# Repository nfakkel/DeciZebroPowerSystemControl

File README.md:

# DeciZebroPowerSystemControl
This repository contains the microcontroller firmware code, the data analysis code and schematics. All are discussed in the Bachelor Thesis: Development of Power System Control for the DeciZebro

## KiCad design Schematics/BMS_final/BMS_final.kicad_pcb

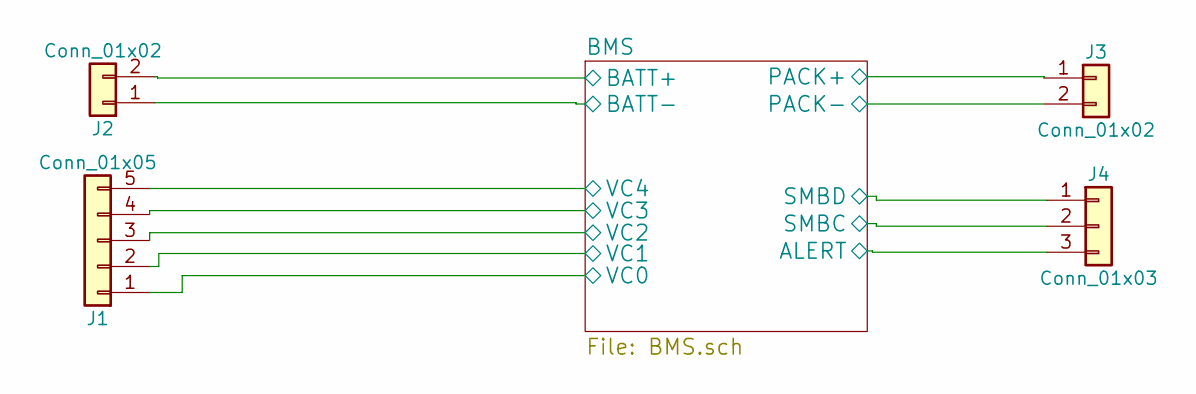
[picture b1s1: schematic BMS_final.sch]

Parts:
J1: Conn_01x05; JST_XH_B05B-XH-A_05x2.50mm_Straight
J2, J3: Conn_01x02; JST_VH_B2P-VH-FB-B_2x3.96mm_Vertical
J4: Conn_01x03; Pin_Header_Straight_1x03_Pitch2.54mm

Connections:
/BMS/ALERT: J4.3; also elsewhere on the board
/BMS/BATT+: J1.5, J2.2; also elsewhere on the board
/BMS/BATT-: J1.1, J2.1; also elsewhere on the board
/BMS/PACK+: J3.1; also elsewhere on the board
/BMS/PACK-: J3.2; also elsewhere on the board
/BMS/SMBC: J4.2; also elsewhere on the board
/BMS/SMBD: J4.1; also elsewhere on the board
/BMS/VC1: J1.2; also elsewhere on the board
/BMS/VC2: J1.3; also elsewhere on the board
/BMS/VC3: J1.4; also elsewhere on the board

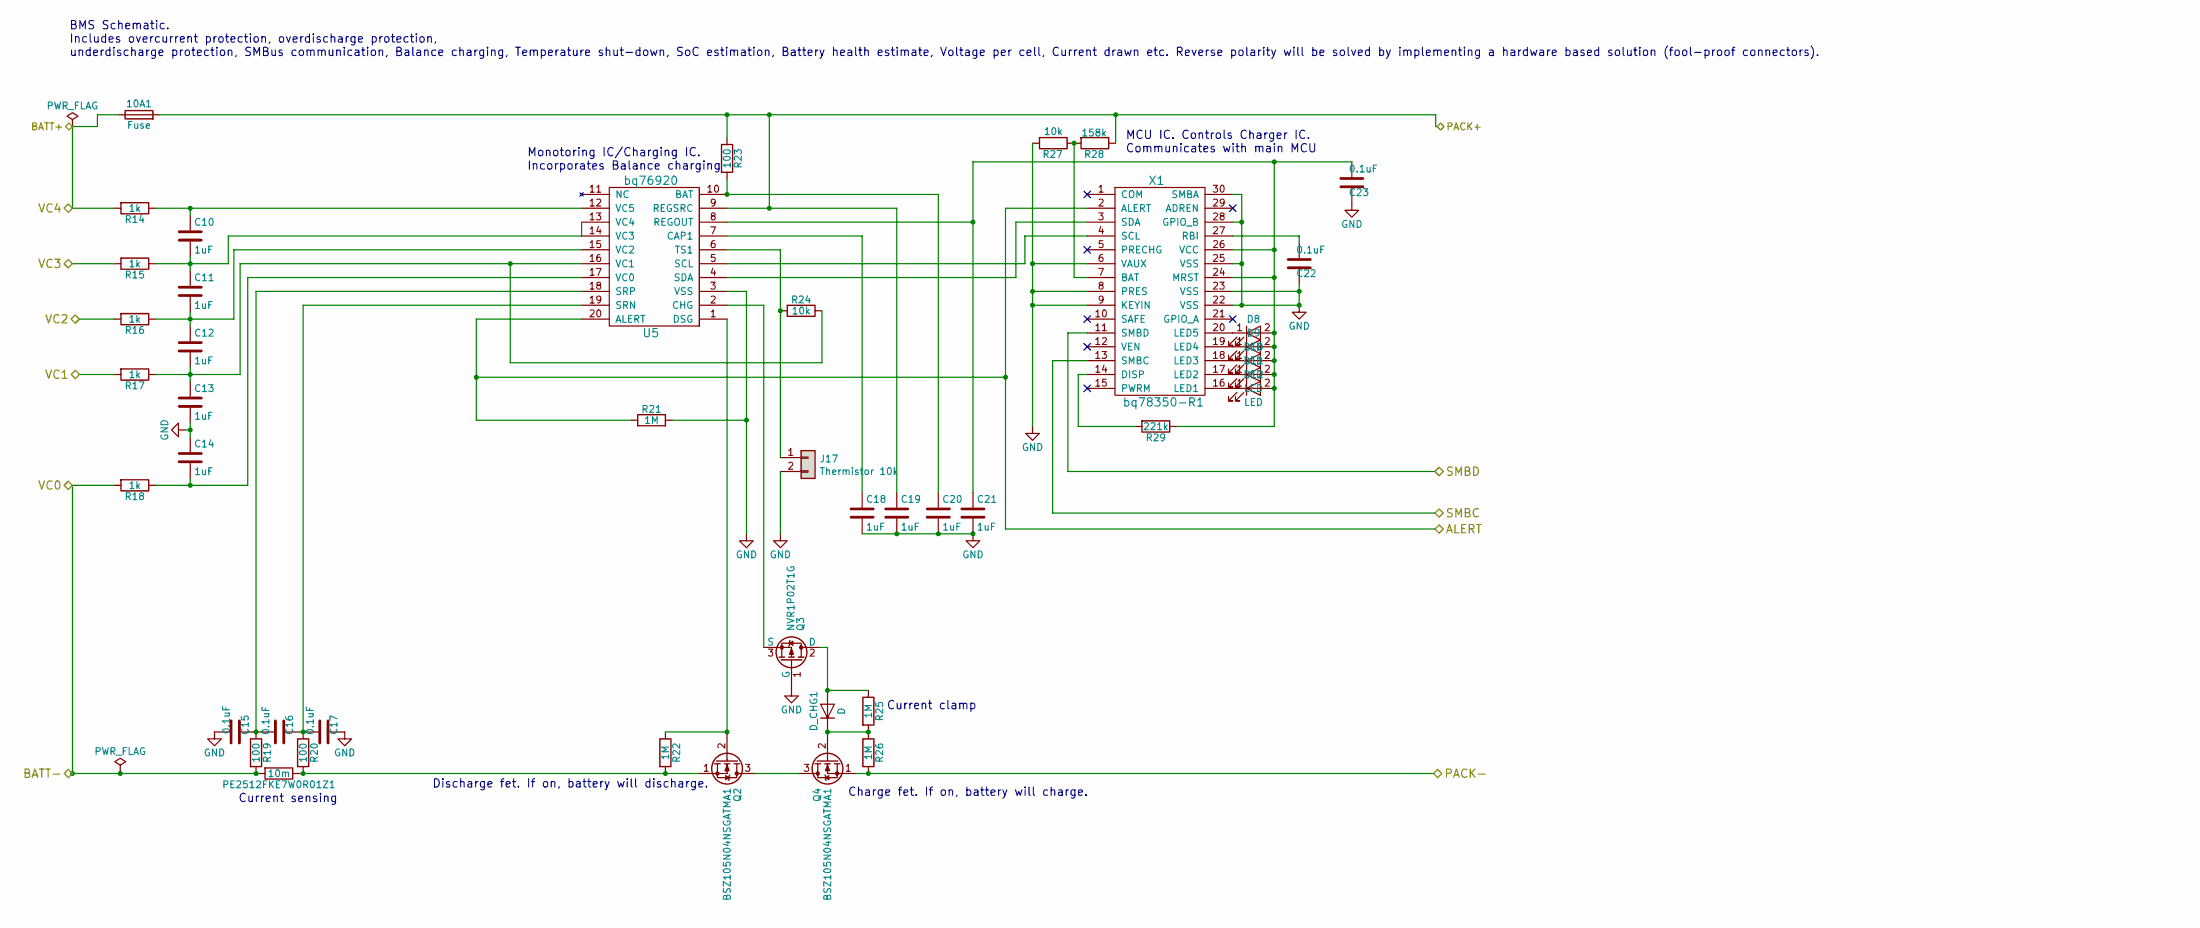
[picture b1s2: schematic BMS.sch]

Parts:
10A1: Fuse
C10, C11, C12, C13, C14, C18, C19, C20, C21: 1uF; C_0603
C15, C16, C17, C22, C23: 0.1uF; C_0402
D8, D9, D10, D11, D12: LED; LED_0603
D_CHG1: D; D_SOD-323
J17: Thermistor 10k; PINHEAD1-2
PE2512FKE7W0R01Z1: 10m; R_2512
Q2, Q4: BSZ105N04NSGATMA1; TO-263-2
Q3: NVR1P02T1G; SOT-23
R14, R15, R16, R17, R18: 1k; R_0402
R19, R20, R23: 100; R_0402
R21, R22, R25, R26: 1M; R_0603
R24, R27: 10k; R_0603
R28: 158k; R_0603
R29: 221k; R_0603
U5: bq76920; TSSOP-20_4.4x6.5mm_Pitch0.65mm
X1: bq78350-R1; TSSOP-30_4.4x7.8mm_P0.5mm

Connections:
/BMS/ALERT: R21.1, U5.20 (ALERT), X1.2 (ALERT); also elsewhere on the board
/BMS/BATT+: 10A1.1, R14.2; also elsewhere on the board
/BMS/BATT-: PE2512FKE7W0R01Z1.2, R18.2, R19.2; also elsewhere on the board
/BMS/PACK+: 10A1.2, C19.1, R23.1, R28.1, U5.9 (REGSRC); also elsewhere on the board
/BMS/PACK-: Q4.1 (S), R26.2; also elsewhere on the board
/BMS/SMBC: X1.13 (SMBC); also elsewhere on the board
/BMS/SMBD: X1.11 (SMBD); also elsewhere on the board
/BMS/VC1: R17.2; also elsewhere on the board
/BMS/VC2: R16.2; also elsewhere on the board
/BMS/VC3: R15.2; also elsewhere on the board
GND: C13.2, C14.1, C15.2, C17.1, C18.2, C19.2, C20.2, C21.2, C22.1, C23.1, J17.2, Q3.1 (G), R21.2, R27.2, U5.3 (VSS), X1.6 (VAUX), X1.8 (PRES), X1.9 (KEYIN), X1.22 (VSS), X1.23 (VSS), X1.25 (VSS), X1.28 (GPIO_B), X1.30 (SMBA)
unnamed: C10.1, R14.1, U5.12 (VC5)
unnamed: C10.2, C11.1, R15.1, U5.13 (VC4), U5.14 (VC3)
unnamed: C11.2, C12.1, R16.1, U5.15 (VC2)
unnamed: C12.2, C13.1, R17.1, R24.1, U5.16 (VC1)
unnamed: C14.2, R18.1, U5.17 (VC0)
unnamed: C15.1, C16.2, R19.1, U5.18 (SRP)
unnamed: C16.1, C17.2, R20.1, U5.19 (SRN)
unnamed: C18.1, U5.7 (CAP1)
unnamed: C20.1, R23.2, U5.10 (BAT)
unnamed: C21.1, C23.2, D8.2 (A), D9.2 (A), D10.2 (A), D11.2 (A), D12.2 (A), R29.1, U5.8 (REGOUT), X1.24 (MRST), X1.26 (VCC)
unnamed: C22.2, X1.27 (RBI)
unnamed: D8.1 (K), X1.20 (LED5)
unnamed: D9.1 (K), X1.19 (LED4)
unnamed: D10.1 (K), X1.18 (LED3)
unnamed: D11.1 (K), X1.17 (LED2)
unnamed: D12.1 (K), X1.16 (LED1)
unnamed: D_CHG1.1 (K), Q4.2 (G), R25.2, R26.1
unnamed: D_CHG1.2 (A), Q3.2 (D), R25.1
unnamed: J17.1, R24.2, U5.6 (TS1)
unnamed: PE2512FKE7W0R01Z1.1, Q2.1 (S), R20.2, R22.2
unnamed: Q2.2 (G), R22.1, U5.1 (DSG)
unnamed: Q2.3 (D), Q4.3 (D)
unnamed: Q3.3 (S), U5.2 (CHG)
unnamed: R27.1, R28.2, X1.7 (BAT)
unnamed: R29.2, X1.14 (DISP)
unnamed: U5.4 (SDA), X1.3 (SDA)
unnamed: U5.5 (SCL), X1.4 (SCL)

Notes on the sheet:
Charge fet. If on, battery will charge.
Discharge fet. If on, battery will discharge.
Current clamp
Current sensing
Monotoring IC/Charging IC. Incorporates Balance charging
MCU IC. Controls Charger IC. Communicates with main MCU
BMS Schematic. Includes overcurrent protection, overdischarge protection, underdischarge protection, SMBus communication, Balance charging, Temperature shut-down, SoC estimation, Battery health estimate, Voltage per cell, Current drawn etc. Reverse polarity will be solved by implementing a hardware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

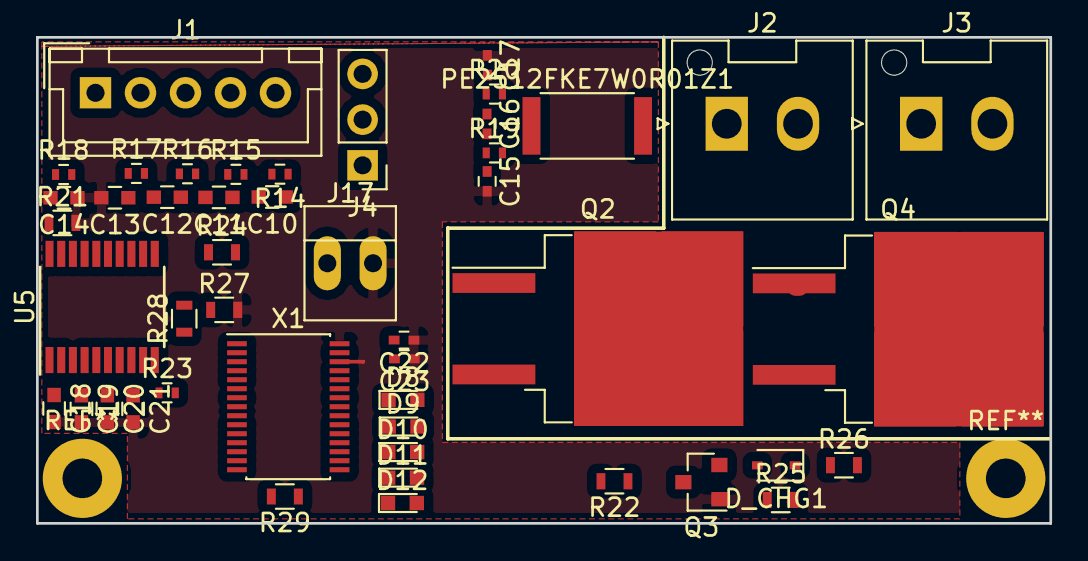
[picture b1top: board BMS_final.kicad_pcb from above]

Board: 4 copper layers, 56.3 x 27.0 mm, 47 parts (0 on the bottom side), 38 nets.

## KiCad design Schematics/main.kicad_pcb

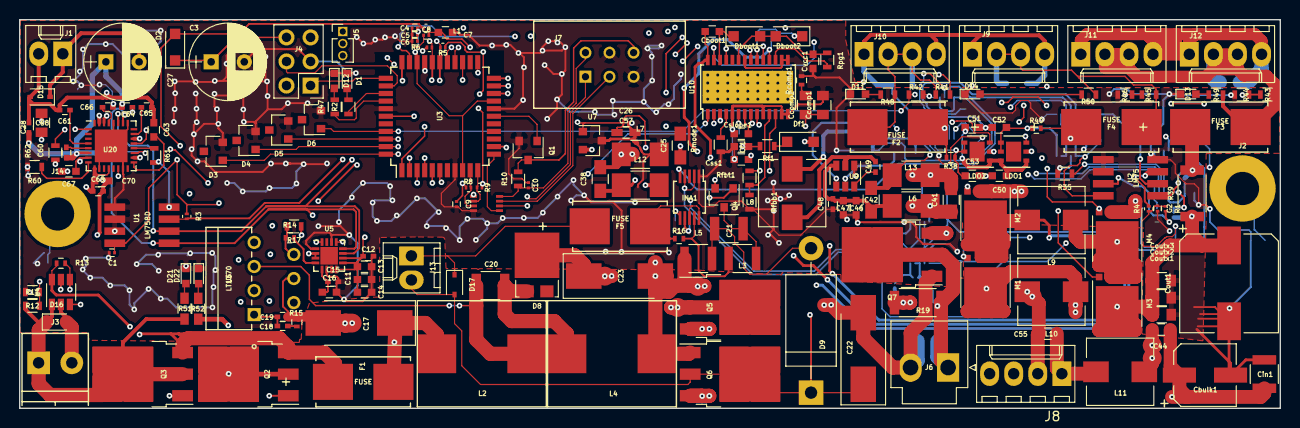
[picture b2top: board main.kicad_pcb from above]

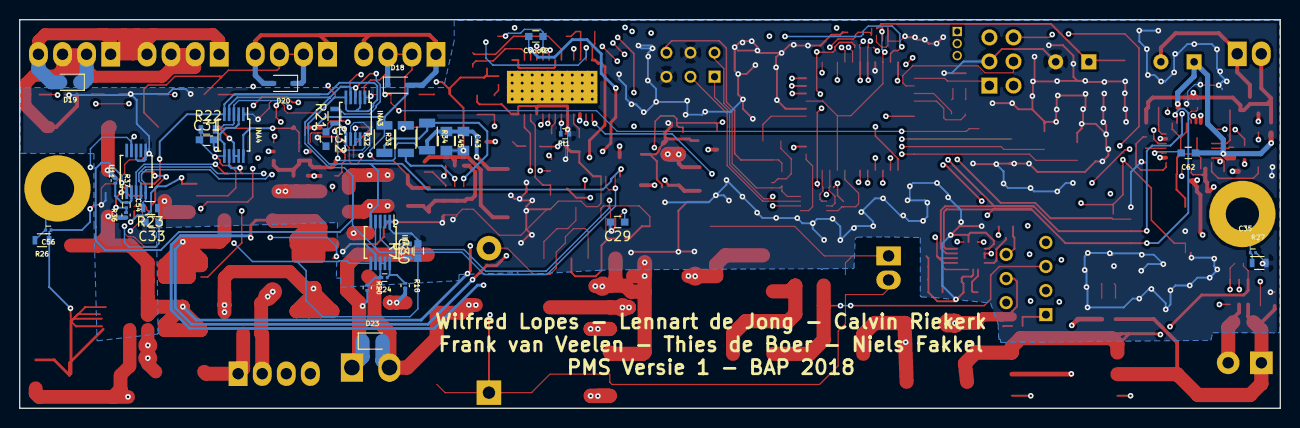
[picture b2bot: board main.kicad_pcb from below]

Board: 4 copper layers, 133.0 x 41.0 mm, 218 parts (35 on the bottom side), 131 nets.

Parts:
C1, C2, C10: 0.1u; C_0201
C3: 1m; CP_Radial_D8.0mm_P3.50mm
C4, C5, C6, C8, C9, C24, C26: .1u; C_0201
C7, C13, C14, C16: 10u; C_0603
C11: 0.1u; C_0603
C12, C15: 0.1u; C_0402
C17, C22, C23: 47u; CP_Tantalum_Case-X_EIA-7343-43_Hand
C18, C19: 4.7n; C_0402
C20, C21: 2.2u; C_1210
C25, C38: 4.7u; C_0805_HandSoldering
C27: 150u; CP_Radial_D8.0mm_P3.50mm
C28: 1.8n; C_0402
C29, C30, C31, C32, C33: .1u; C_0603
C35, C54, C56: 0.1uF; C_0201
C41, C42: 4.7uF; C_0805_HandSoldering
C43, C45: 22uF; C_0805
C44, C55: 1uF; C_0603_HandSoldering
C46, C47, C50, C51, C52, C53: 10uF; C_0603
C48, C49: 0.1uF; C_0402
C57: 10u; C_0603_HandSoldering
C60, C61: 10 nF; C_0402
C62, C63: 0.47 uF; C_0603
C64, C65: 22 nF; C_0402
C66, C69: 1 uF; C_0402
C67: 0.1 uF; C_0603
C68: 22 uF; C_0805
C70: 4.7 uF; C_0603
Cboot1, Cboot2: 100nF; C_0603
Cbulk1: 68uF; CP_Elec_6.3x7.7
Ccomp1: 91pF; C_0805
Ccomp2: 15nF; C_0805
Cf1: 100nF; C_0603
Cin1: 10uF; C_1210
Cout1: 150uF; CP_Elec_10x10.5
Coutx1, Coutx2, Coutx3: 22uF; C_0805
Cslope1: 110pF; C_0603
Css1: 15nF; C_0603
Cvcc1: 1uF; C_0603
D1, D11, D12, D13, D14, D21, D22: LED; LED_0603
D2: D_Schottky; D_SOD-123F
D3, D4, D5, D6: D_Zener; SOT-23
D8: PMEG100V060ELPDZ; TO-277A
D9: MBR360G; D_DO-201_P15.24mm_Horizontal
D15, D16, D17, D18, D19, D20, D23: D_TVS_ALT; D_SOD-323
Dboot1, Dboot2: Zener; D_SOD-123F
Df1: Schottky; D_SOD-123F
F1, F2, F4, F5: FUSE; 0154001.DR
F3: FUSE; 0154005.DR
INA1, INA2, INA3, INA4: INA226; VSSOP-10_3x3mm_Pitch0.5mm
J1: Qi; Molex_KK-6410-02_02x2.54mm_Straight
J2, J14: Mounting hole; MountingHole_3.5mm_Pad
J3: Laptop interface; TerminalBlock_Phoenix_PT-3.5mm_2pol
J4: Debug_Interface; Pin_Header_Straight_2x03_Pitch2.54mm
J5: BMS_DATA_IN; Pin_Header_Straight_1x03_Pitch1.27mm
J6: BMS_POWER_IN; JST_VH_B2P-VH_2x3.96mm_Vertical
J7: ZebroBus_Interface; ZebroBus
J8: Switch_Connector; Molex_KK-6410-04_04x2.54mm_Straight
J9: 5V; Molex_KK-6410-04_04x2.54mm_Straight
J10: 3.3V; Molex_KK-6410-04_04x2.54mm_Straight
J11: 16V_2; Molex_KK-6410-04_04x2.54mm_Straight
J12: 16V_1; Molex_KK-6410-04_04x2.54mm_Straight
J13: Solar; Molex_KK-6410-02_02x2.54mm_Straight
L1: Ferrite_Bead; R_0201
L2, L4: 10u; coil1115x1000
L3, L5: 10u; L_1210
L6, L7, L12, L13: 270n; L_1210_HandSoldering
L8: 3.3uH; L_Wuerth_HCI-7040
L9: 2.20uH; L_Wuerth_HCI-7040
L10, L11: 2.2uH; L_Wuerth_HCI-7040
LDO1: LP38692-5V; WSON-6-1EP_3x3mm_Pitch0.95mm
LDO2: LP38692-3V3; WSON-6-1EP_3x3mm_Pitch0.95mm
M1: CSD17310Q5A; VSONP-8-1EP_5x6_Pitch1.27mm
M2: CSD18514Q5A; VSONP-8-1EP_5x6_Pitch1.27mm
M3: CSD16321Q5; VSONP-8-1EP_5x6_Pitch1.27mm
M4: CSD18511Q5A; VSONP-8-1EP_5x6_Pitch1.27mm
Q1: Si2302CDS; SOT-23
Q2, Q3, Q5, Q6: IPD85P04P4-07; TO-252-3_TabPin2
Q4: BSS316N H6327; SOT-23
Q7: IPD85P04-07; TO-252-3_TabPin2
R1, R3, R4, R5, R6: 10k; R_0201
R2, R47, R48: 120; R_0603
R7, R21, R22, R23: 10k; R_0603
R8, R9: 2.7k; R_0201
R10, R11, R43, R62: 100k; R_0603
R12: 12k; R_0603
R13: 470k; R_0402
R14: 11k; R_0402
R15: 2k; R_0402
R16: 100m; R_0402
R17, R42, R45: 60k; R_0603
R18, R20, R36, R37: 10; R_0201
R19: 5m; R_2010
R26, R27: 1M; R_0603
R32, R33: 10k; R_1206
R34: 75k; R_1206
R35: 2k; R_0603
R38, R40: 50m; R_0402
R39: 10m; R_2010
R41, R46: 40k; R_0603
R44: 11k; R_0603
R49: 1.4k; R_0603
R50: 300; R_0603
R51: 1.4k; R_0603_HandSoldering
R52: 500; R_0603_HandSoldering
R60, R61: 20k; R_0603
Rcomp1: 10.2k; R_0402
Rf1: 10; R_0603
Rfbb1: 20k; R_0603
Rfbt1: 383k; R_0603
Rmode1: 93.1k; R_0603
Rpg1: 10k; R_0603
Rt1: 23.2k; R_0402
U1: LM75BD; SO-8
U2: LM75; SO-8
U3: ATXMEGA32A4U-AU; tqfp44_v1
U4: LTC4412; TSOT-23-6
U5: AD5121; LFCSP-16-1EP_3x3mm_Pitch0.5mm
U6: LT1370; LT1370CT7
U7: LM3480-3.3; SOT-23
U9: TPS565201; SOT-23-6
U10: LM5176; HTSSOP-28_4.4x9.7mm_Pitch0.65mm_ThermalPad
U11: INA300; VSSOP-10_3x3mm_Pitch0.5mm
U12: TCA9803; VSSOP-8
U20: P9025AC; QFN-32-1EP_5x5mm_Pitch0.5mm

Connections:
+3V3: C1.1, C2.1, C9.1, C11.1, C12.1, C13.1, C14.1, C26.1, C29.1, C30.1, C31.1, C32.1, C33.1, C57.1, D2.2, INA1.6, INA2.6, INA3.6, INA4.2, INA4.6, J4.6, R1.1, R3.1, R4.1, R5.1, R6.1, R7.1, R8.1, R9.1, R21.1, R22.1, R23.1, R33.2, U1.8, U2.8, U5.7, U5.8, U5.9, U5.10, U5.13, U5.16, U7.1, U11.9, U12.1
/Control/3.3V_enable: LDO2.3, U3.20
/Control/3.3V_fuse: D6.1, R41.2, R42.1, U3.41
/Control/5V_enable: LDO1.3, U3.21
/Control/5V_fuse: D5.1, R45.2, R46.1, U3.42
/Control/16V_enable: U3.22, U11.4
/Control/16V_fuse: D4.1, R43.2, R44.1, U3.43
/Control/ALERT: J5.3, U3.23
/Control/INTERRUP_ZEBROBUS: J7.6, Q1.3, R10.2
/Control/OC_3.3V: INA3.3, R21.2, U3.1
/Control/OC_5V: INA4.3, R22.2, U3.2
/Control/OC_16V: R23.2, U3.3, U10.1, U11.5
/Control/PDI_CLK: J4.4, U3.35
/Control/PDI_DATA: J4.1, U3.34
/Control/REF_ZEBROBUS: C10.1, J7.2, R10.1, U12.8
/Control/RX: J4.2, U3.26
/Control/SCL_ZEBROBUS: J7.3, U12.7
/Control/SDA_ZEBROBUS: J7.1, U12.6
/Control/TX: J4.5, U3.27
/Control/bus_alert: INA2.3, R7.2, U3.4
/Control/pwm_solar: Q4.1, U3.13
/Control/v_laptop: D3.1, R11.2, R12.1, U3.44
/Input/INPUT_SEL: U3.6, U4.3
/Input/LAPTOP_IN+: D16.1, J3.1, Q3.2, R11.1, R51.1, U4.1
/Input/LAPTOP_IN-: C17.2, C19.2, C23.1, C67.2, C68.2, C69.2, C70.2, D8.3, D16.2, J3.2, Q5.2, R15.2, U4.2, U5.2, U5.3, U6.4, U20.18, U20.22, U20.31
/Input/POT_OUT: R14.1, R17.2, U6.6
/Input/QI_IN+: C69.1, C70.1, Q2.2, R52.1, R62.1, U20.9, U20.12
/Input/solar_in+: D17.1, F5.1, J13.1
/Input/solar_in-: C22.1, D9.1, D17.2, J13.2, Q4.2, Q6.2
/Output/3.3V+: D18.1, F2.2, J10.2, J10.3, R41.1, R48.1
/Output/3.3V-: C42.2, C50.2, C51.2, C52.2, C53.2, D18.2, D20.2, J9.1, J9.4, J10.1, J10.4, L13.1, LDO1.2, LDO2.2, R32.2
/Output/5V+: D20.1, F4.2, J9.2, J9.3, R45.1, R50.1
/Output/16V+: D19.1, F3.2, J11.2, J11.3, J12.2, J12.3, R43.1, R49.1
/Output/16V-: C44.2, D19.2, J11.1, J11.4, J12.1, J12.4, L11.1
/Output/POWER_BUS+: C41.1, C55.1, J8.2, L6.2, L10.2
/Output/POWER_BUS-: C41.2, C55.2, J8.1, L11.2, L13.2
/PowerBus/BMS_POWERBUS_+: D23.1, J6.1, Q7.2, R19.2, R20.2
/PowerBus/BMS_POWERBUS_-: C22.2, C23.2, C38.2, D23.2, J6.2, J8.4, L4.1, L5.1, L7.1, Q5.1, Q6.1, Q7.1, R17.1
/PowerBus/INPUT_POWERBUS+: Q5.3, Q6.3, R18.2, R19.1
/PowerBus/OUTPUT_POWERBUS_+: C38.1, J8.3, L12.1, Q7.3
/QI_charging/COIL_IN+: C27.2, D15.1, J1.1
/QI_charging/COIL_IN-: C28.2, C61.2, C63.2, C65.2, D15.2, J1.2, U20.30
/QI_charging/EN_MCU_QI: U3.25, U20.14
/QI_charging/INT_MCU_QI: R62.2, U3.5, U20.1
/QI_charging/SCL_MCU_QI: INA1.5, INA2.5, INA3.2, INA3.5, INA4.5, J5.2, R6.2, U1.2, U2.2, U3.29, U5.11, U20.27
/QI_charging/SDA_MCU_QI: INA1.2, INA1.4, INA2.4, INA3.4, INA4.4, J5.1, R5.2, U1.1, U2.1, U3.28, U5.12, U20.26
GND: C1.2, C2.2, C3.2, C4.2, C5.2, C6.2, C7.1, C8.2, C9.2, C10.2, C11.2, C12.2, C13.2, C14.2, C15.2, C16.2, C25.2, C26.2, C29.2, C30.2, C31.2, C32.2, C33.2, C35.1, C43.2, C45.2, C46.1, C47.1, C48.1, C56.1, C57.2, C66.2, Cbulk1.2, Ccomp1.2, Cf1.2, Cin1.2, Cout1.2, Coutx1.2, Coutx2.2, Coutx3.2, Cslope1.2, Css1.2, Cvcc1.2, D1.1, D3.2, D4.2, D5.2, D6.2, D11.1, D12.1, D13.1, D14.1, D21.1, D22.1, INA1.1, INA1.7, INA2.1, INA2.2, INA2.7, INA3.1, INA3.7, INA4.1, INA4.7, J4.3, J7.4, J7.5, L7.2, Q1.2, R12.2, R26.1, R27.1, R35.2, R42.2, R44.2, R46.2, R60.2, R61.2, Rcomp1.2, Rfbb1.1, Rmode1.2, Rt1.2, U1.4, U1.5, U1.6, U1.7, U2.4, U2.5, U2.6, U3.8, U3.18, U3.30, U3.38, U5.1, U5.6, U5.14, U7.3, U9.1, U10.5, U10.10, U10.13, U10.14, U10.15, U10.16, U10.22, U11.6, U11.8, U12.4, U20.10, U20.15, U20.25, U20.28, U20.33
unnamed: C3.1, C4.1, C5.1, C6.1, D2.1, L1.1, U3.9, U3.19, U3.31
unnamed: C7.2, C8.1, L1.2, U3.39
unnamed: C15.1, C16.1, U5.5
unnamed: C17.1, F1.2, L2.2, U6.7
unnamed: C18.1, C19.1, U6.1
unnamed: C18.2, R15.1
unnamed: C20.1, L2.1, U6.5
unnamed: C20.2, D8.2, L4.2
unnamed: C21.1, L3.1, Q4.3
unnamed: C21.2, D9.2, L5.2
unnamed: C24.1, INA2.10, R18.1
unnamed: C24.2, INA2.8, INA2.9, R20.1
unnamed: C25.1, L12.2, U7.2
unnamed: C27.1, C28.1, C60.1, C62.1, C64.1, U20.6
unnamed: C35.2, J14.1, R27.2
unnamed: C42.1, C46.2, C47.2, C48.2, L6.1, U9.3
unnamed: C43.1, C45.1, C50.1, C51.1, L8.2, LDO1.1, LDO1.6, LDO2.1, LDO2.6, R34.2
unnamed: C44.1, Cbulk1.1, Cin1.1, Df1.2, L10.1, M1.3, U10.3
unnamed: C49.1, L8.1, U9.2
unnamed: C49.2, U9.6
unnamed: C52.1, INA4.10, LDO1.4, LDO1.5, R40.1
unnamed: C53.1, INA3.10, LDO2.4, LDO2.5, R38.1
unnamed: C54.1, R37.2, U11.2
unnamed: C54.2, R36.2, U11.1
unnamed: C56.2, J2.1, R26.2
unnamed: C60.2, U20.5
unnamed: C61.1, U20.4
unnamed: C62.2, U20.19
unnamed: C63.1, U20.17
unnamed: C64.2, U20.21
unnamed: C65.1, U20.23
unnamed: C66.1, U20.29
unnamed: C67.1, C68.1, U20.7
unnamed: Cboot1.1, L9.2, M1.1, M2.3, U10.28
unnamed: Cboot1.2, Dboot1.1, U10.26
unnamed: Cboot2.1, Dboot2.1, U10.20
unnamed: Cboot2.2, L9.1, M3.1, M4.3, U10.18
unnamed: Ccomp1.1, Ccomp2.1, U10.9
unnamed: Ccomp2.2, Rcomp1.1
unnamed: Cf1.1, Rf1.2, U10.2
unnamed: Cout1.1, Coutx1.1, Coutx2.1, Coutx3.1, M3.3, R36.1, R39.1, Rfbt1.1, U10.12
unnamed: Cslope1.1, U10.7
unnamed: Css1.1, U10.8
unnamed: Cvcc1.1, Dboot1.2, Dboot2.2, Rpg1.1, U10.23
unnamed: D1.2, R2.2
unnamed: D11.2, R48.2
unnamed: D12.2, R47.2
unnamed: D13.2, R49.2
unnamed: D14.2, R50.2
unnamed: D21.2, R51.2
unnamed: D22.2, R52.2
unnamed: Df1.1, Rf1.1
unnamed: F1.1, Q2.3, Q3.3, R13.1, U4.6
unnamed: F2.1, INA3.8, INA3.9, R38.2
unnamed: F3.1, R37.1, R39.2
unnamed: F4.1, INA4.8, INA4.9, R40.2
unnamed: F5.2, INA1.8, INA1.10, R16.1
unnamed: INA1.9, L3.2, R16.2
unnamed: M1.2, U10.27
unnamed: M2.1, M4.1
unnamed: M2.2, U10.25
unnamed: M3.2, U10.19
unnamed: M4.2, U10.21
unnamed: Q1.1, U3.17
unnamed: Q2.1, R13.2, U4.4
unnamed: Q3.1, U4.5
unnamed: R1.2, U2.7
unnamed: R2.1, U3.36
unnamed: R3.2, U1.3, U3.33
unnamed: R4.2, U2.3, U3.32
unnamed: R8.2, U3.10, U12.3
unnamed: R9.2, U3.11, U12.2
unnamed: R14.2, U5.4
unnamed: R32.1, R34.1, U9.4
unnamed: R33.1, U9.5
unnamed: R35.1, U11.3
unnamed: R47.1, U3.37
unnamed: R60.1, U20.8
unnamed: R61.1, U20.20
unnamed: Rfbb1.2, Rfbt1.2, U10.11
unnamed: Rmode1.1, U10.4
unnamed: Rpg1.2, U10.17
unnamed: Rt1.1, U10.6
unnamed: U3.12, U12.5

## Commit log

2018-07-03 Final PMS firmware

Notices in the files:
parts and their libraries:
Copyright 2016 Accelerated Designs. All rights reserved.
